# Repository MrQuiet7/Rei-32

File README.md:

# Rei-32(レイ-32)
### Minimal STM32 Development Board

## Overview

 - A compact STM32 development board designed from scratch with a focus on simplicity, usability, and a clean form factor.
 -  If there’s no need for a feature, it simply isn’t included.
 -  The complete hardware design was created in **KiCad 10**, including the schematic and PCB layout.
 -  **Small board. Simple design. Full control.**

## Features

- STM32 microcontroller
- USB connectivity
- On-board WS2812B addressable LED
- Exposed GPIO pins
- Compact PCB layout
- Open hardware design

## Hardware
- Rei-32 is built around an **STM32F103C8T6** microcontroller, providing an ARM-based platform in a compact and practical form factor.

## Form Factor
- Rei-32 has dimensions of 25mm by 55mm (0.98 inches by 2.17 inches for Americans).

<p align="center">
    PCB  +  Front  +  Front with components  +  Back
</p>

- The compact layout allows it to be used in projects where a larger development board would be inconvenient.

## Boot Configuration
- Rei-32 includes dedicated configuration for the STM32 boot modes.
- The boot configuration is accessible directly on the board, allowing the MCU to be placed into the required boot mode without adding external circuitry.

## Status LED
- An addressable WS2812B LED is included on the board.
- It can be used as a simple status indicator or controlled directly by firmware for debugging, state indication, and user feedback.

## Schematic
- The complete schematic is included in the repository.

## Author
- **Hossein Sharifi**
- Designed, developed, and documented as a personal hardware project.

## License
#### GNU General Public License v3.0

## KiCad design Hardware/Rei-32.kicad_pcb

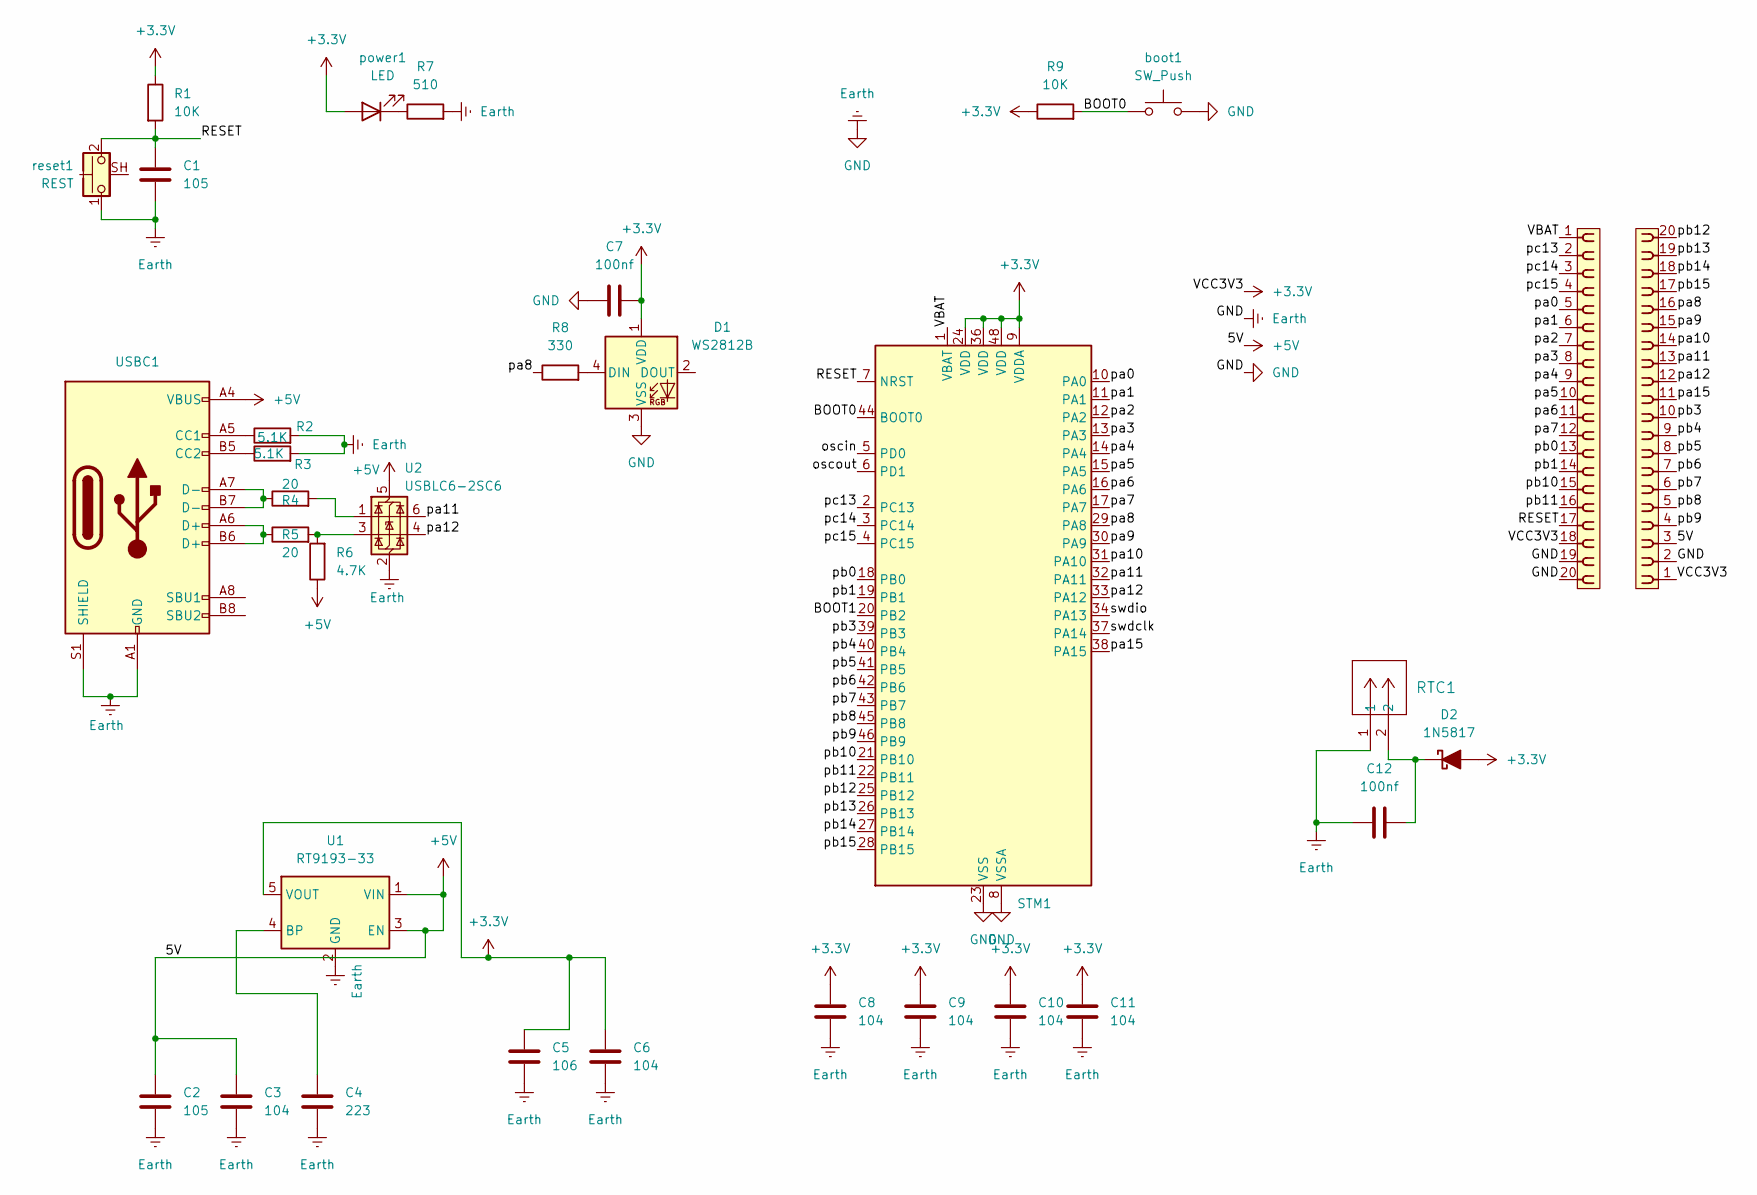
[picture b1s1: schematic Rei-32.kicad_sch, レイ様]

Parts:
C1, C2: 105; C_0201_0603Metric
C3, C6, C8, C9, C10, C11: 104; C_0201_0603Metric
C4: 223; C_0201_0603Metric
C5: 106; C_0201_0603Metric
C7, C12: 100nf; C_0201_0603Metric
D1: WS2812B; LED_WS2812B_PLCC4_5.0x5.0mm_P3.2mm
D2: 1N5817; D_0201_0603Metric
P1: PINHD_1x20_Female; PinSocket_1x20_P2.54mm_Vertical
R1, R9: 10K; R_0201_0603Metric
R2, R3: 5.1K; R_0201_0603Metric
R4, R5: 20; R_0201_0603Metric
R6: 4.7K; R_0201_0603Metric
R7: 510; R_0201_0603Metric
R8: 330; R_0201_0603Metric
RTC1: CONN_505568_02_MOL
STM1: STM32F103C8Tx; LQFP-48_7x7mm_P0.5mm
U1: RT9193-33; TSOT-23-5
U2: USBLC6-2SC6; SOT-23-6
USBC1: USB_C_Receptacle_USB2.0_16P; USB_C_Receptacle_G-Switch_GT-USB-7010ASV
boot1: SW_Push; SW_DIP_SPSTx01_Slide_6.7x4.1mm_W6.73mm_P2.54mm_LowProfile_J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
p2: PINHD_1x20_Female; PinSocket_1x20_P2.54mm_Vertical
power1: LED; LED_0603_1608Metric
reset1: REST; SW_SPST_CK_KMS2xxG

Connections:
+3.3V: C5.2, C6.2, C7.1, C8.1, C9.1, C10.1, C11.1, D1.1 (VDD), D2.2 (A), P1.18, R1.1, R9.1, STM1.9 (VDDA), STM1.24 (VDD), STM1.36 (VDD), STM1.48 (VDD), U1.5 (VOUT), p2.1, power1.2 (A)
+5V: C2.2, C3.2, R6.1, U1.1 (VIN), U1.3 (EN), U2.5 (VBUS), USBC1.A4 (VBUS), USBC1.A9 (VBUS), USBC1.B4 (VBUS), USBC1.B9 (VBUS), p2.3
/BOOT0: R9.2, STM1.44 (BOOT0), boot1.1
/BOOT1: STM1.20 (PB2)
/RESET: C1.1, P1.17, R1.2, STM1.7 (NRST), reset1.2
/VBAT: P1.1, STM1.1 (VBAT)
/oscin: STM1.5 (PD0)
/oscout: STM1.6 (PD1)
/pa0: P1.5, STM1.10 (PA0)
/pa1: P1.6, STM1.11 (PA1)
/pa2: P1.7, STM1.12 (PA2)
/pa3: P1.8, STM1.13 (PA3)
/pa4: P1.9, STM1.14 (PA4)
/pa5: P1.10, STM1.15 (PA5)
/pa6: P1.11, STM1.16 (PA6)
/pa7: P1.12, STM1.17 (PA7)
/pa8: R8.1, STM1.29 (PA8), p2.16
/pa9: STM1.30 (PA9), p2.15
/pa10: STM1.31 (PA10), p2.14
/pa11: STM1.32 (PA11), U2.6 (I/O1), p2.13
/pa12: STM1.33 (PA12), U2.4 (I/O2), p2.12
/pa15: STM1.38 (PA15), p2.11
/pb0: P1.13, STM1.18 (PB0)
/pb1: P1.14, STM1.19 (PB1)
/pb3: STM1.39 (PB3), p2.10
/pb4: STM1.40 (PB4), p2.9
/pb5: STM1.41 (PB5), p2.8
/pb6: STM1.42 (PB6), p2.7
/pb7: STM1.43 (PB7), p2.6
/pb8: STM1.45 (PB8), p2.5
/pb9: STM1.46 (PB9), p2.4
/pb10: P1.15, STM1.21 (PB10)
/pb11: P1.16, STM1.22 (PB11)
/pb12: STM1.25 (PB12), p2.20
/pb13: STM1.26 (PB13), p2.19
/pb14: STM1.27 (PB14), p2.18
/pb15: STM1.28 (PB15), p2.17
/pc13: P1.2, STM1.2 (PC13)
/pc14: P1.3, STM1.3 (PC14)
/pc15: P1.4, STM1.4 (PC15)
/swdclk: STM1.37 (PA14)
/swdio: STM1.34 (PA13)
Earth: C1.2, C2.1, C3.1, C4.1, C5.1, C6.1, C7.2, C8.2, C9.2, C10.2, C11.2, C12.2, D1.3 (VSS), P1.19, P1.20, R2.2, R3.2, R7.2, RTC1.1, RTC1.3, RTC1.4, STM1.8 (VSSA), STM1.23 (VSS), STM1.35 (VSS), STM1.47 (VSS), U1.2 (GND), U2.2 (GND), USBC1.A1 (GND), USBC1.A12 (GND), USBC1.B1 (GND), USBC1.B12 (GND), USBC1.S1 (SHIELD), USBC1.SH, boot1.2, p2.2, reset1.1, reset1.SH (B)
unnamed: D1.4 (DIN), R8.2
unnamed: C12.1, D2.1 (K), RTC1.2
unnamed: R4.1, USBC1.A7 (D-), USBC1.B7 (D-)
unnamed: R4.2, U2.1 (I/O1)
unnamed: R5.1, USBC1.A6 (D+), USBC1.B6 (D+)
unnamed: R5.2, R6.2, U2.3 (I/O2)
unnamed: C4.2, U1.4 (BP)
unnamed: R2.1, USBC1.A5 (CC1)
unnamed: R3.1, USBC1.B5 (CC2)
unnamed: R7.1, power1.1 (K)

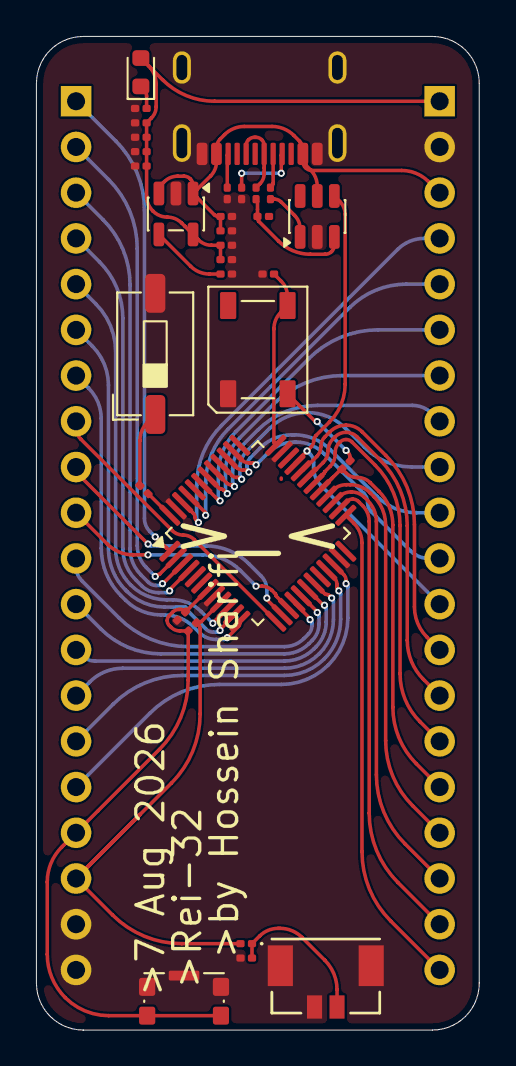
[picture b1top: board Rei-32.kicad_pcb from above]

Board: 2 copper layers, 24.6 x 55.2 mm, 33 parts (0 on the bottom side), 48 nets.
